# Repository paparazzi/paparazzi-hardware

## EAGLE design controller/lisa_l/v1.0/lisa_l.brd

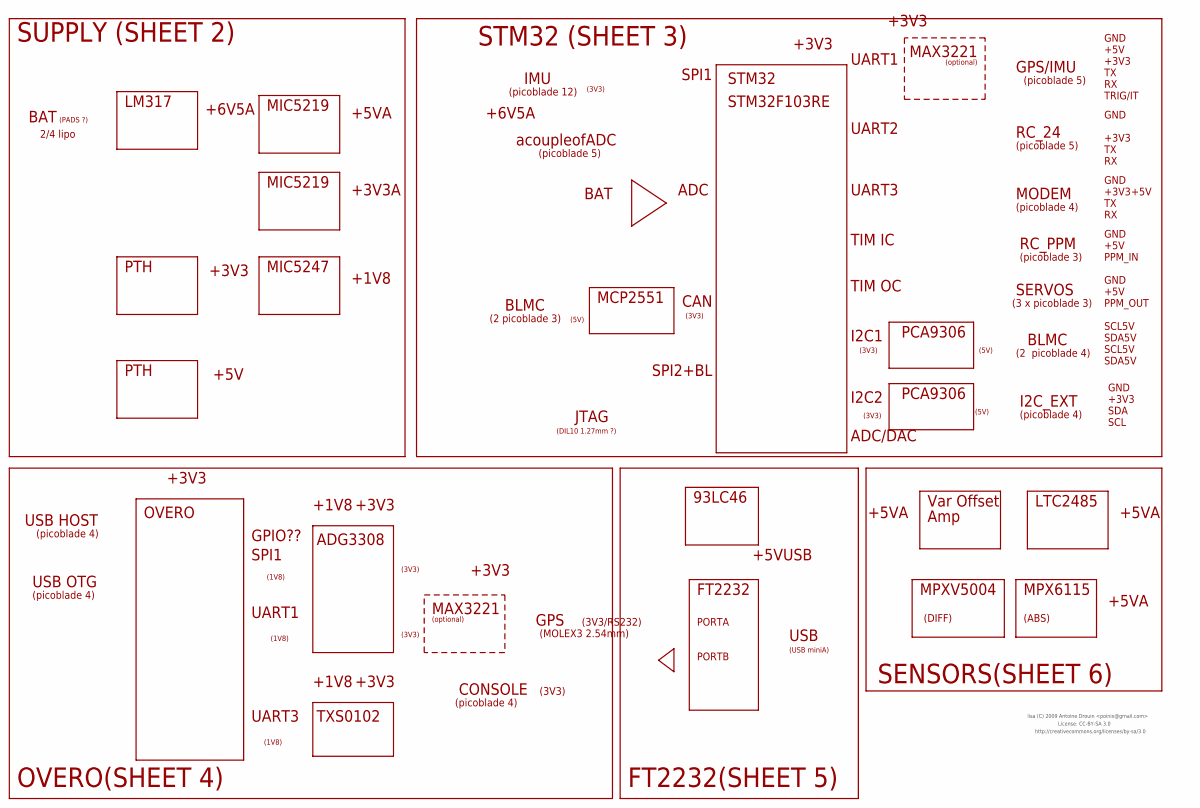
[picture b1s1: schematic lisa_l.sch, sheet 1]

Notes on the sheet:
SUPPLY (SHEET 2)
STM32 (SHEET 3)
OVERO(SHEET 4)
UART3
ADG3308
SPI1
UART1
OVERO
STM32
PTH
LM317
+5V
+3V3
+6V5A
BAT
IMU
MAX3221
GPS
(3V3/RS232)
(1V8)
(3V3)
SPI2+BL
SENSORS(SHEET 6)
JTAG
(PADS ?)
(picoblade 12)
2/4 lipo
(DIL10 1.27mm ?)
GPS/IMU
(picoblade 5)
(MOLEX3 2.54mm)
UART2
MODEM
TIM IC
RC_PPM
(picoblade 3)
FT2232
TIM OC
SERVOS
(3 x picoblade 3)

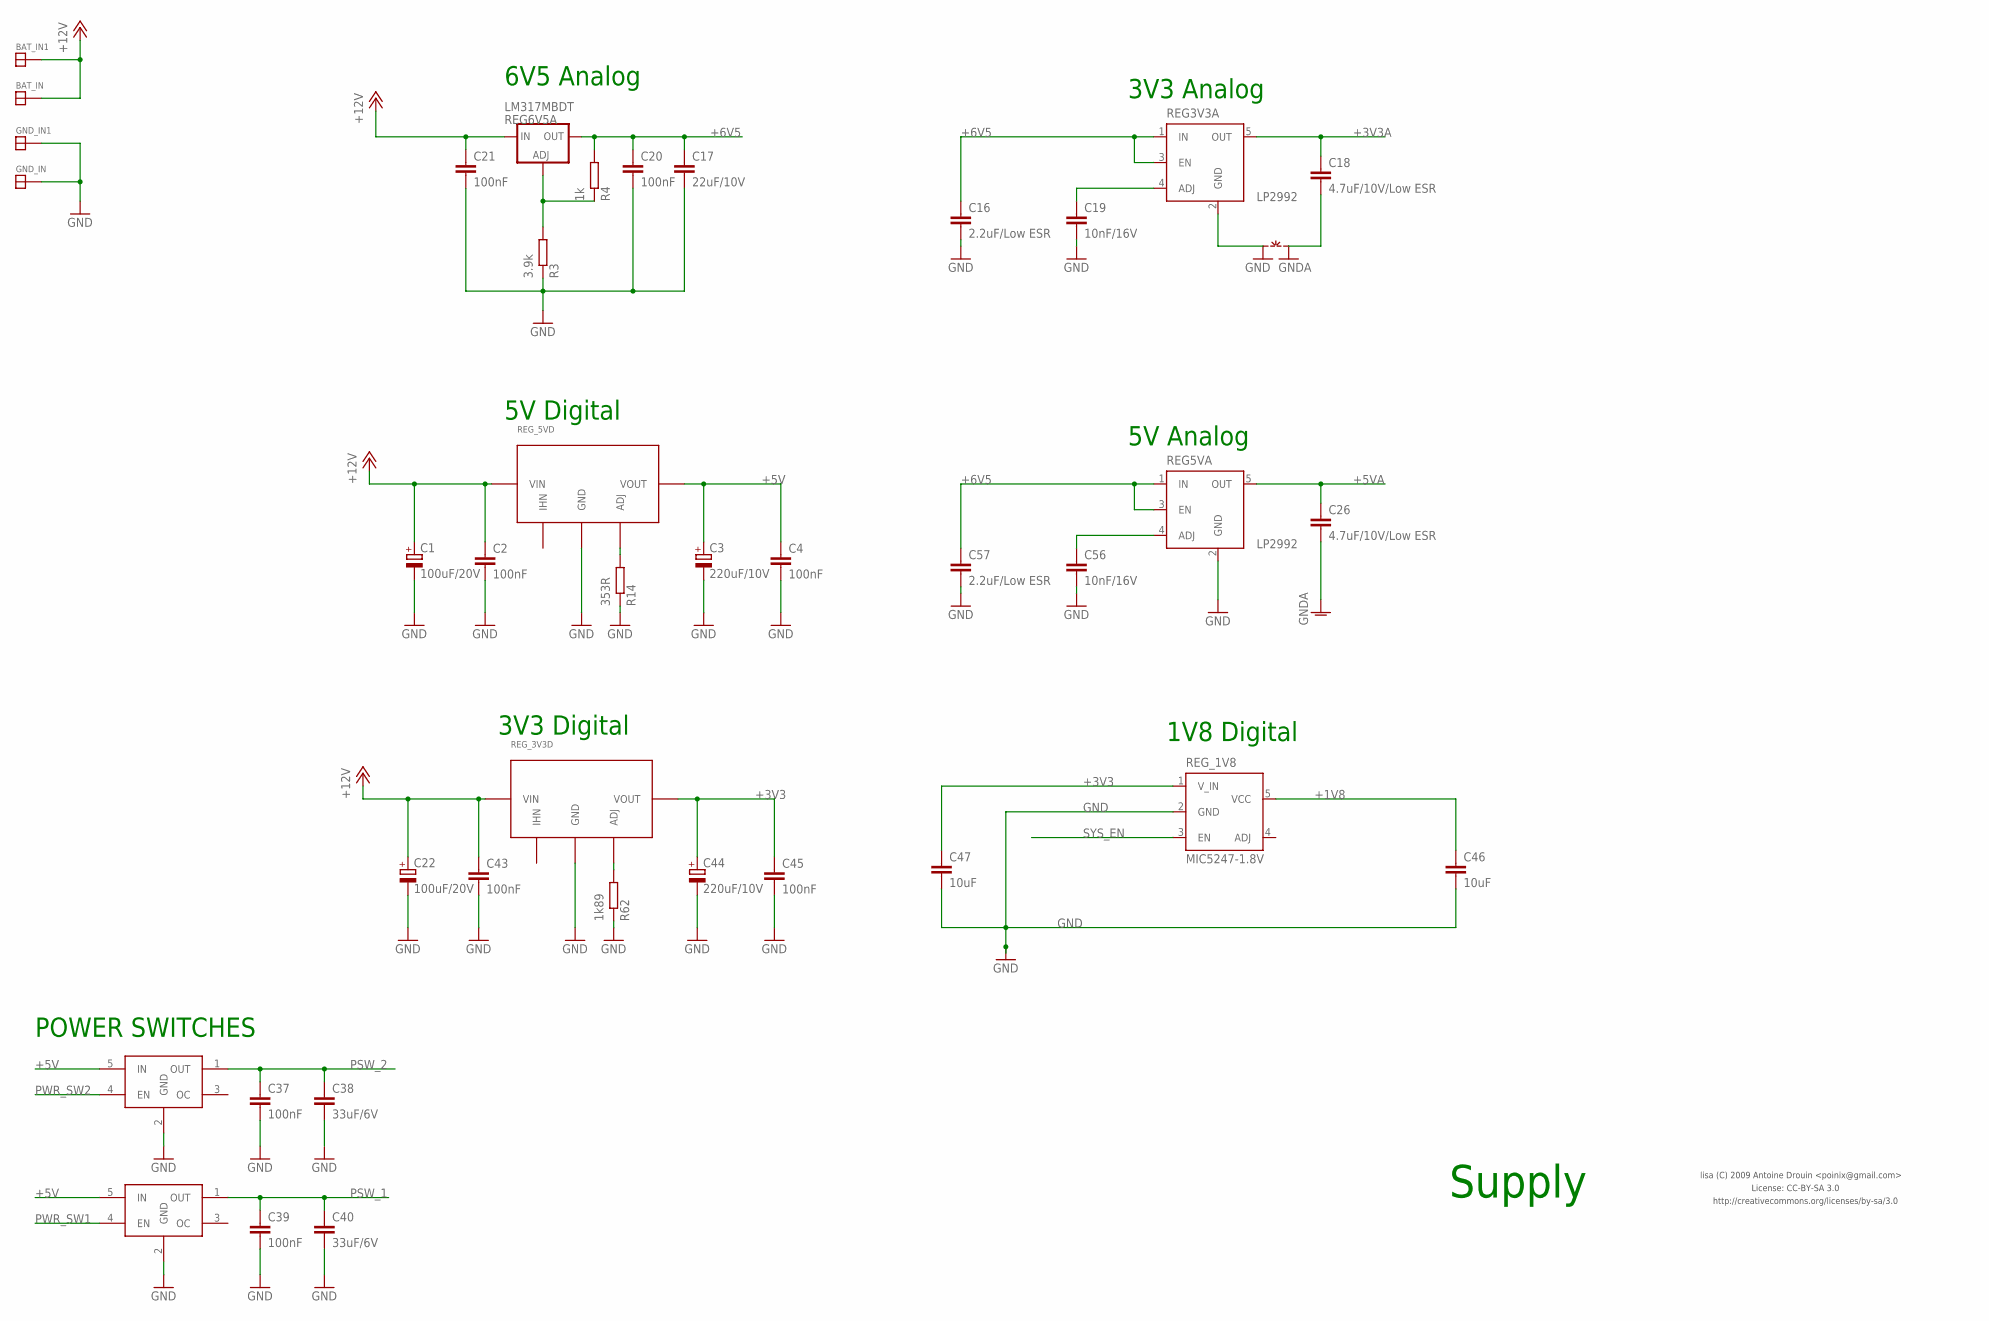
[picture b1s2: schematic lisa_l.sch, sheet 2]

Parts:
BAT_IN, BAT_IN1: SOLDER_PAD150_75; SOLD_PAD_150_75
C1, C22: 100uF/20V; 7343/D
C2, C4, C20, C21, C37, C39, C43, C45: 100nF; 0603-CAP
C3, C44: 220uF/10V; 7343/D
C16, C57: 2.2uF/Low ESR; 0603-CAP
C17: 22uF/10V; 1206-CAP
C18, C26: 4.7uF/10V/Low ESR; 0603-CAP
C19, C56: 10nF/16V; 0603-CAP
C38, C40: 33uF/6V; 1206-CAP
C46, C47: 10uF; 0603-CAP
GND_IN, GND_IN1: SOLDER_PAD150_75; SOLD_PAD_150_75
PWS1, PWS2: TPS2051B; SOT23-5L
R3: 3.9k; 0603-RES
R4: 1k; 0603-RES
R14: 353R; 0603-RES
R62: 1k89; 0603-RES
REG3V3A, REG5VA: LP2992; SOT23-5
REG6V5A: LM317MBDT; DPACK
REG_1V8: MIC5247-1.8V; SOT-23-5
REG_3V3D, REG_5VD: PTHTH; PTH_TH
~NUDEV~1: GND-GNDA

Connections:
+1V8: C46.P$1 (1), REG_1V8.5 (VCC); also elsewhere on the board
+3V3: C44.+, C45.P$1 (1), C47.P$1 (1), REG_1V8.1 (V_IN), REG_3V3D.P$3 (VOUT); also elsewhere on the board
+3V3A: C18.P$1 (1), REG3V3A.5 (OUT); also elsewhere on the board
+5V: C3.+, C4.P$1 (1), PWS1.5 (IN), PWS2.5 (IN), REG_5VD.P$3 (VOUT); also elsewhere on the board
+5VA: C26.P$1 (1), REG5VA.5 (OUT); also elsewhere on the board
+6V5: C16.P$1 (1), C17.P$1 (1), C20.P$1 (1), C57.P$1 (1), R4.P$2 (2), REG3V3A.1 (IN), REG3V3A.3 (EN), REG5VA.1 (IN), REG5VA.3 (EN), REG6V5A.4 (OUT); also elsewhere on the board
+12V: BAT_IN.P$1, BAT_IN1.P$1, C1.+, C2.P$1 (1), C21.P$1 (1), C22.+, C43.P$1 (1), REG6V5A.3 (IN), REG_3V3D.P$1 (VIN), REG_5VD.P$1 (VIN); also elsewhere on the board
GND: C1.-, C2.P$2 (2), C3.-, C4.P$2 (2), C16.P$2 (2), C17.P$2 (2), C19.P$2 (2), C20.P$2 (2), C21.P$2 (2), C22.-, C37.P$2 (2), C38.P$2 (2), C39.P$2 (2), C40.P$2 (2), C43.P$2 (2), C44.-, C45.P$2 (2), C46.P$2 (2), C47.P$2 (2), C56.P$2 (2), C57.P$2 (2), GND_IN.P$1, GND_IN1.P$1, PWS1.2 (GND), PWS2.2 (GND), R3.P$1 (1), R14.P$1 (1), R62.P$1 (1), REG3V3A.2 (GND), REG5VA.2 (GND), REG_1V8.2 (GND), REG_3V3D.P$2 (GND), REG_5VD.P$2 (GND), ~NUDEV~1.GND; also elsewhere on the board
GNDA: C18.P$2 (2), C26.P$2 (2), ~NUDEV~1.GNDA; also elsewhere on the board
unnamed: R62.P$2 (2), REG_3V3D.P$4 (ADJ)
unnamed: C56.P$1 (1), REG5VA.4 (ADJ)
unnamed: C19.P$1 (1), REG3V3A.4 (ADJ)
unnamed: R3.P$2 (2), R4.P$1 (1), REG6V5A.1 (ADJ)
PSW_1: C39.P$1 (1), C40.P$1 (1), PWS1.1 (OUT); also elsewhere on the board
PSW_2: C37.P$1 (1), C38.P$1 (1), PWS2.1 (OUT); also elsewhere on the board
PWR_SW1: PWS1.4 (EN); also elsewhere on the board
PWR_SW2: PWS2.4 (EN); also elsewhere on the board
RIPRIP: R14.P$2 (2), REG_5VD.P$4 (ADJ)
SYS_EN: REG_1V8.3 (EN); also elsewhere on the board

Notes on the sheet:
5V Digital
6V5 Analog
3V3 Analog
POWER SWITCHES
3V3 Digital
1V8 Digital
Supply
License: CC-BY-SA 3.0
http://creativecommons.org/licenses/by-sa/3.0
lisa (C) 2009 Antoine Drouin <poinix@gmail.com>
5V Analog

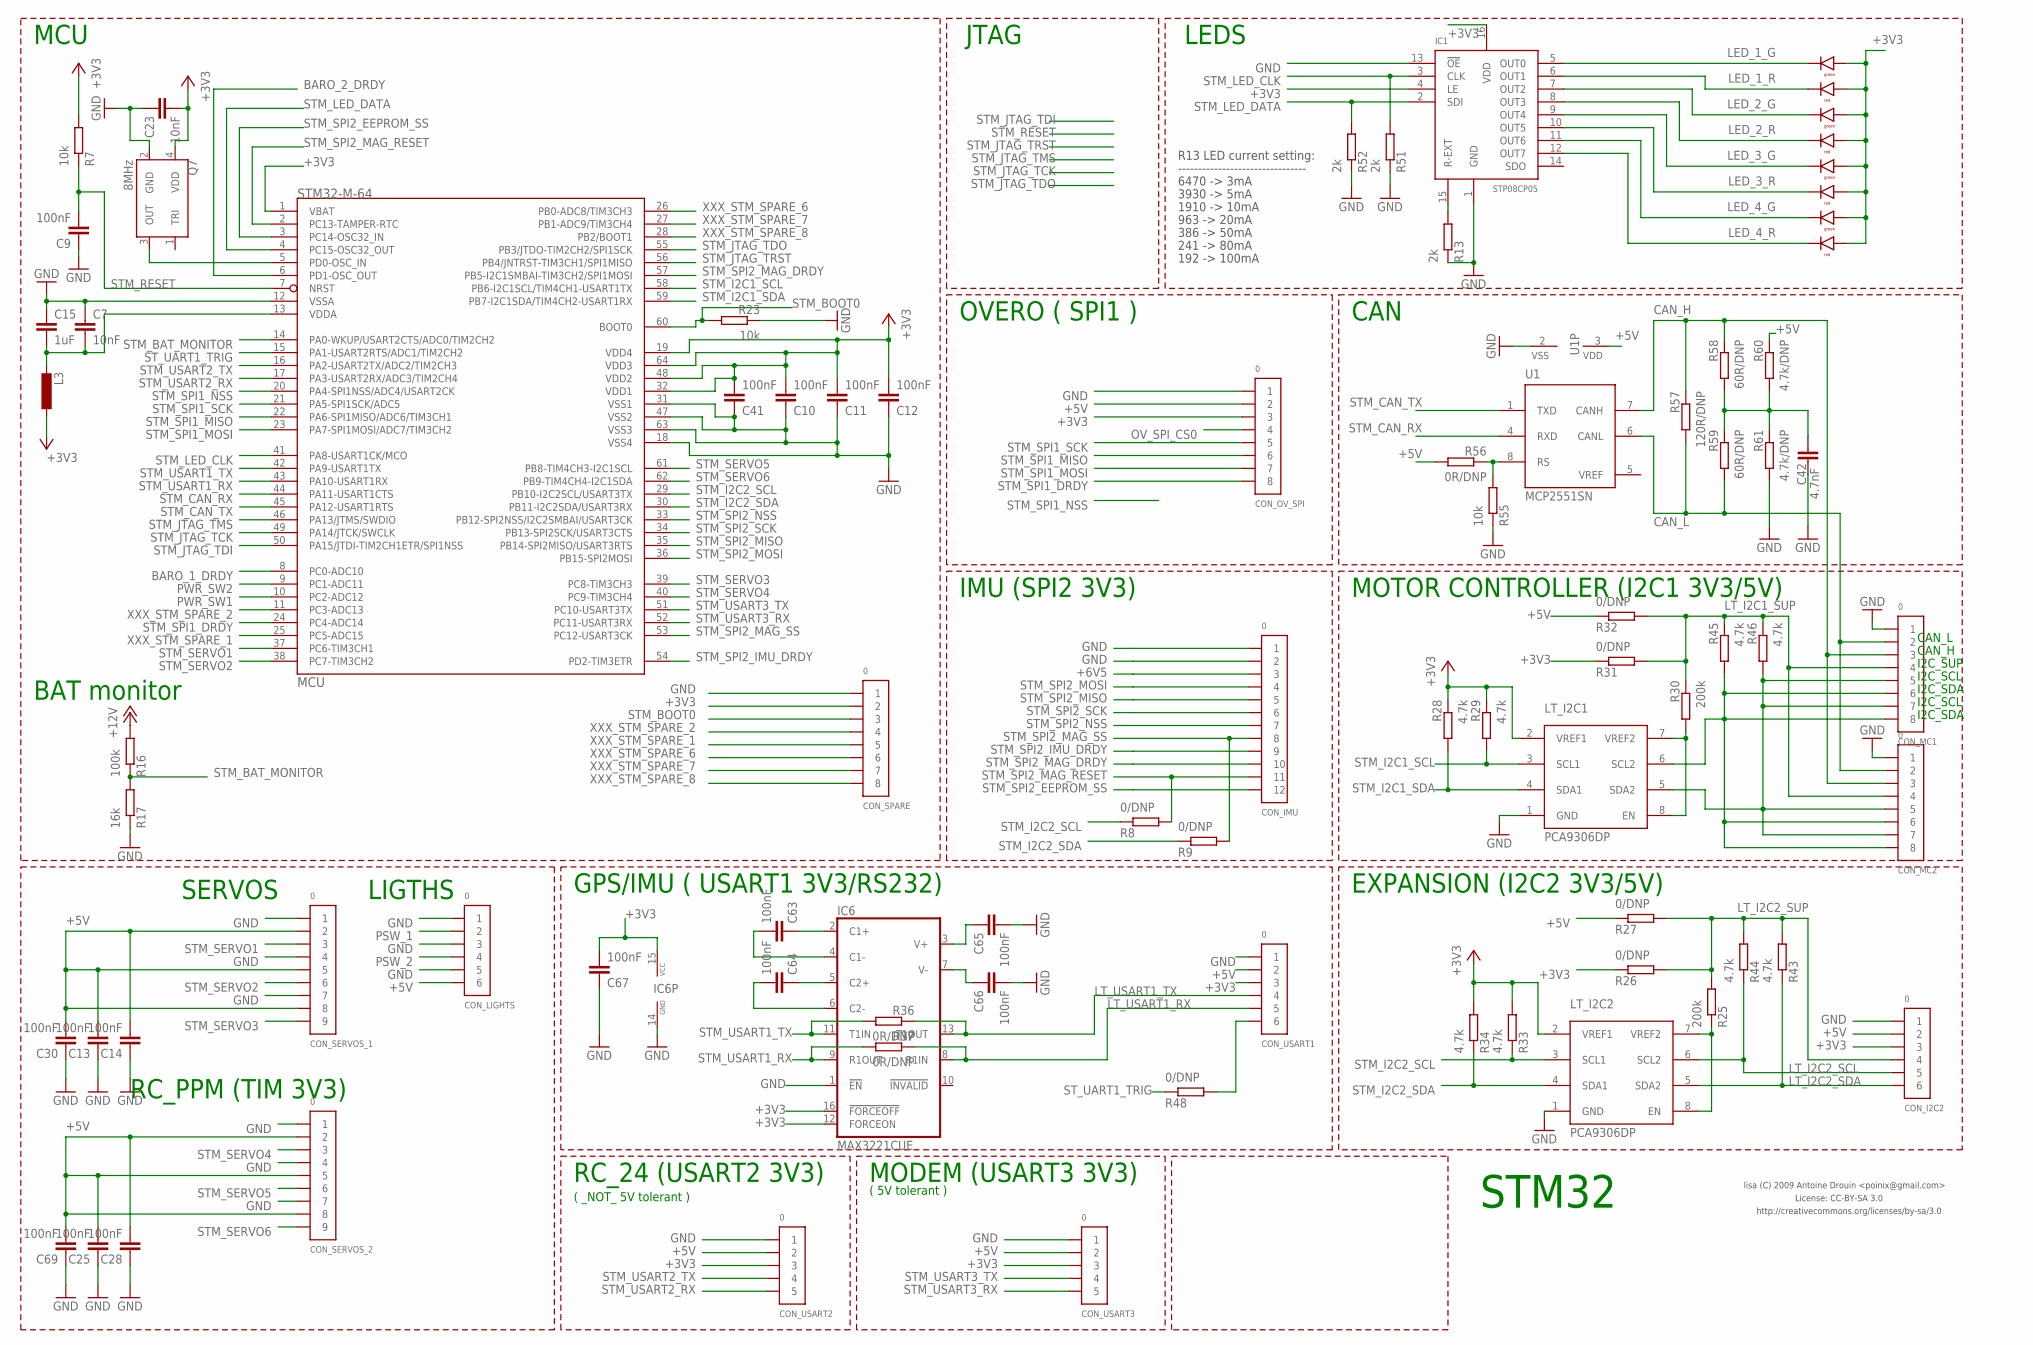
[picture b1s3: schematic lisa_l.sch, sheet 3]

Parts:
C7, C23: 10nF; 0603-CAP
C9, C10, C11, C12, C13, C14, C25, C28, C30, C41, C63, C64, C65, C66, C67, C69: 100nF; 0603-CAP
C15: 1uF; 0603-CAP
C42: 4.7nF; 0603-CAP
CON_I2C2: 0; PB-53261-06
CON_IMU: 0; PB-53398-12
CON_LIGHTS: 0; PB-53261-06
CON_MC1, CON_MC2: 0; PB-53261-08
CON_OV_SPI: 0; PB-53398-08
CON_SERVOS_1, CON_SERVOS_2: 0; PB-53261-09
CON_SPARE: 0; PB-53261-08
CON_USART1: 0; PB-53398-06
CON_USART2, CON_USART3: 0; PB-53261-05
IC1: STP08CP05; TSSOP16
IC6: MAX3221CUE; TSSOP16
L3: INDUCTOR-0603; 0603-IND
LED_1, LED_2, LED_3, LED_4: LED_DUO; DUO_LED
LT_I2C1, LT_I2C2: PCA9306DP; TSSOP_B3
MCU: STM32-M-64; LQFP64
Q7: 8MHz; ASE_OSCILLATOR
R7, R23, R55: 10k; 0603-RES
R8, R9, R26, R27, R31, R32, R48: 0/DNP; 0603-RES
R13, R51, R52: 2k; 0603-RES
R16: 100k; 0603-RES
R17: 16k; 0603-RES
R25, R30: 200k; 0603-RES
R28, R29, R33, R34, R43, R44, R45, R46: 4.7k; 0603-RES
R36, R37, R56: 0R/DNP; 0603-RES
R57: 120R/DNP; 0603-RES
R58, R59: 60R/DNP; 0603-RES
R60, R61: 4.7k/DNP; 0603-RES
U1: MCP2551SN; SO-08

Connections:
+3V3: C10.P$2 (2), C11.P$2 (2), C12.P$2 (2), C23.P$2 (2), C41.P$2 (2), C67.P$2 (2), CON_I2C2.3, CON_OV_SPI.3, CON_SPARE.2, CON_USART1.3, CON_USART2.3, CON_USART3.3, IC1.4 (LE), IC1.16 (VDD), IC6.12 (FORCEON), IC6.15 (VCC), IC6.16 (!FORCEOFF), L3.P$1 (1), LED_1.1, LED_1.4, LED_2.1, LED_2.4, LED_3.1, LED_3.4, LED_4.1, LED_4.4, LT_I2C1.2 (VREF1), LT_I2C2.2 (VREF1), MCU.1 (VBAT), MCU.19 (VDD4), MCU.32 (VDD1), MCU.48 (VDD2), MCU.64 (VDD3), Q7.4 (VDD), R7.P$2 (2), R26.P$1 (1), R28.P$1 (1), R29.P$1 (1), R31.P$1 (1), R33.P$2 (2), R34.P$2 (2); also elsewhere on the board
+5V: C13.P$2 (2), C14.P$2 (2), C25.P$2 (2), C28.P$2 (2), C30.P$2 (2), C69.P$2 (2), CON_I2C2.2, CON_LIGHTS.6, CON_OV_SPI.2, CON_SERVOS_1.2, CON_SERVOS_1.5, CON_SERVOS_1.8, CON_SERVOS_2.2, CON_SERVOS_2.5, CON_SERVOS_2.8, CON_USART1.2, CON_USART2.2, CON_USART3.2, R27.P$1 (1), R32.P$1 (1), R56.P$2 (2), R60.P$1 (1), U1.3 (VDD); also elsewhere on the board
+6V5: CON_IMU.3; also elsewhere on the board
+12V: R16.P$2 (2); also elsewhere on the board
BARO_1_DRDY: MCU.8 (PC0-ADC10); also elsewhere on the board
BARO_2_DRDY: MCU.6 (PD1-OSC_OUT); also elsewhere on the board
CAN_H: CON_MC1.3, CON_MC2.3, R57.P$1 (1), R58.P$1 (1), U1.7 (CANH)
CAN_L: CON_MC1.2, CON_MC2.2, R57.P$2 (2), R59.P$2 (2), U1.6 (CANL)
GND: C7.P$1 (1), C9.P$1 (1), C10.P$1 (1), C11.P$1 (1), C12.P$1 (1), C13.P$1 (1), C14.P$1 (1), C15.P$1 (1), C23.P$1 (1), C25.P$1 (1), C28.P$1 (1), C30.P$1 (1), C41.P$1 (1), C42.P$1 (1), C65.P$2 (2), C66.P$2 (2), C67.P$1 (1), C69.P$1 (1), CON_I2C2.1, CON_IMU.1, CON_IMU.2, CON_LIGHTS.1, CON_LIGHTS.3, CON_LIGHTS.5, CON_MC1.1, CON_MC2.1, CON_OV_SPI.1, CON_SERVOS_1.1, CON_SERVOS_1.4, CON_SERVOS_1.7, CON_SERVOS_2.1, CON_SERVOS_2.4, CON_SERVOS_2.7, CON_SPARE.1, CON_USART1.1, CON_USART2.1, CON_USART3.1, IC1.1 (GND), IC1.13 (!OE), IC6.1 (!EN), IC6.14 (GND), LT_I2C1.1 (GND), LT_I2C2.1 (GND), MCU.12 (VSSA), MCU.18 (VSS4), MCU.31 (VSS1), MCU.47 (VSS2), MCU.63 (VSS3), Q7.2 (GND), R13.P$1 (1), R17.P$1 (1), R23.P$1 (1), R51.P$1 (1), R52.P$1 (1), R55.P$1 (1), R61.P$2 (2), U1.2 (VSS); also elsewhere on the board
INT/TRIGGER: CON_USART1.6, R48.P$2 (2)
LED_1_G: IC1.5 (OUT0), LED_1.3
LED_1_R: IC1.6 (OUT1), LED_1.2
LED_2_G: IC1.7 (OUT2), LED_2.3
LED_2_R: IC1.8 (OUT3), LED_2.2
LED_3_G: IC1.9 (OUT4), LED_3.3
LED_3_R: IC1.10 (OUT5), LED_3.2
LED_4_G: IC1.11 (OUT6), LED_4.3
LED_4_R: IC1.12 (OUT7), LED_4.2
LT_I2C1_SUP: CON_MC1.4, CON_MC2.4, R30.P$1 (1), R31.P$2 (2), R32.P$2 (2), R45.P$1 (1), R46.P$1 (1)
LT_I2C2_SCL: CON_I2C2.5, LT_I2C2.6 (SCL2), R44.P$1 (1)
LT_I2C2_SDA: CON_I2C2.6, LT_I2C2.5 (SDA2), R43.P$1 (1)
LT_I2C2_SUP: CON_I2C2.4, R25.P$2 (2), R26.P$2 (2), R27.P$2 (2), R43.P$2 (2), R44.P$2 (2)
LT_USART1_RX: CON_USART1.5, IC6.8 (R1IN), R37.P$1 (1)
LT_USART1_TX: CON_USART1.4, IC6.13 (T1OUT), R36.P$1 (1)
unnamed: IC1.15 (R-EXT), R13.P$2 (2)
unnamed: MCU.5 (PD0-OSC_IN), Q7.3 (OUT)
unnamed: LT_I2C1.7 (VREF2), LT_I2C1.8 (EN), R30.P$2 (2)
unnamed: R55.P$2 (2), R56.P$1 (1), U1.8 (RS)
unnamed: LT_I2C2.7 (VREF2), LT_I2C2.8 (EN), R25.P$1 (1)
unnamed: C42.P$2 (2), R58.P$2 (2), R59.P$1 (1), R60.P$2 (2), R61.P$1 (1)
unnamed: C63.P$1 (1), IC6.2 (C1+)
unnamed: C63.P$2 (2), IC6.4 (C1-)
unnamed: C64.P$1 (1), IC6.5 (C2+)
unnamed: C64.P$2 (2), IC6.6 (C2-)
unnamed: C66.P$1 (1), IC6.7 (V-)
unnamed: C65.P$1 (1), IC6.3 (V+)
OV_SPI_CS0: CON_OV_SPI.4; also elsewhere on the board
PSW_1: CON_LIGHTS.2; also elsewhere on the board
PSW_2: CON_LIGHTS.4; also elsewhere on the board
PWR_SW1: MCU.10 (PC2-ADC12); also elsewhere on the board
PWR_SW2: MCU.9 (PC1-ADC11); also elsewhere on the board
SCL_0_TRANSLATED: CON_MC1.6, CON_MC1.8, CON_MC2.6, CON_MC2.8, LT_I2C1.6 (SCL2), R45.P$2 (2)
SDA_0_TRANSLATED: CON_MC1.5, CON_MC1.7, CON_MC2.5, CON_MC2.7, LT_I2C1.5 (SDA2), R46.P$2 (2)
STM_BAT_MONITOR: MCU.14 (PA0-WKUP/USART2CTS/ADC0/TIM2CH2), R16.P$1 (1), R17.P$2 (2)
STM_BOOT0: CON_SPARE.3, MCU.60 (BOOT0), R23.P$2 (2)
STM_CAN_RX: MCU.44 (PA11-USART1CTS), U1.4 (RXD)
STM_CAN_TX: MCU.45 (PA12-USART1RTS), U1.1 (TXD)
STM_I2C1_SCL: LT_I2C1.3 (SCL1), MCU.58 (PB6-I2C1SCL/TIM4CH1-USART1TX), R29.P$2 (2)
STM_I2C1_SDA: LT_I2C1.4 (SDA1), MCU.59 (PB7-I2C1SDA/TIM4CH2-USART1RX), R28.P$2 (2)
STM_I2C2_SCL: LT_I2C2.3 (SCL1), MCU.29 (PB10-I2C2SCL/USART3TX), R8.P$1 (1), R33.P$1 (1); also elsewhere on the board
STM_I2C2_SDA: LT_I2C2.4 (SDA1), MCU.30 (PB11-I2C2SDA/USART3RX), R9.P$1 (1), R34.P$1 (1); also elsewhere on the board
STM_JTAG_TCK: MCU.49 (PA14/JTCK/SWCLK); also elsewhere on the board
STM_JTAG_TDI: MCU.50 (PA15/JTDI-TIM2CH1ETR/SPI1NSS); also elsewhere on the board
STM_JTAG_TDO: MCU.55 (PB3/JTDO-TIM2CH2/SPI1SCK); also elsewhere on the board
STM_JTAG_TMS: MCU.46 (PA13/JTMS/SWDIO); also elsewhere on the board
STM_JTAG_TRST: MCU.56 (PB4/JNTRST-TIM3CH1/SPI1MISO); also elsewhere on the board
STM_LED_CLK: IC1.3 (CLK), MCU.41 (PA8-USART1CK/MCO), R51.P$2 (2)
STM_LED_DATA: IC1.2 (SDI), MCU.4 (PC15-OSC32_OUT), R52.P$2 (2)
STM_RESET: C9.P$2 (2), MCU.7 (NRST), R7.P$1 (1); also elsewhere on the board
STM_SERVO1: CON_SERVOS_1.3, MCU.37 (PC6-TIM3CH1)
STM_SERVO2: CON_SERVOS_1.6, MCU.38 (PC7-TIM3CH2)
STM_SERVO3: CON_SERVOS_1.9, MCU.39 (PC8-TIM3CH3)
STM_SERVO4: CON_SERVOS_2.3, MCU.40 (PC9-TIM3CH4)
STM_SERVO5: CON_SERVOS_2.6, MCU.61 (PB8-TIM4CH3-I2C1SCL)
STM_SERVO6: CON_SERVOS_2.9, MCU.62 (PB9-TIM4CH4-I2C1SDA)
STM_SPI1_DRDY: CON_OV_SPI.8, MCU.24 (PC4-ADC14); also elsewhere on the board
STM_SPI1_MISO: CON_OV_SPI.6, MCU.22 (PA6-SPI1MISO/ADC6/TIM3CH1); also elsewhere on the board
STM_SPI1_MOSI: CON_OV_SPI.7, MCU.23 (PA7-SPI1MOSI/ADC7/TIM3CH2); also elsewhere on the board
STM_SPI1_NSS: MCU.20 (PA4-SPI1NSS/ADC4/USART2CK); also elsewhere on the board
STM_SPI1_SCK: CON_OV_SPI.5, MCU.21 (PA5-SPI1SCK/ADC5); also elsewhere on the board
STM_SPI2_EEPROM_SS: CON_IMU.12, MCU.3 (PC14-OSC32_IN)
STM_SPI2_IMU_DRDY: CON_IMU.9, MCU.54 (PD2-TIM3ETR)
STM_SPI2_MAG_DRDY: CON_IMU.10, MCU.57 (PB5-I2C1SMBAI-TIM3CH2/SPI1MOSI)
STM_SPI2_MAG_RESET: CON_IMU.11, MCU.2 (PC13-TAMPER-RTC), R8.P$2 (2)
STM_SPI2_MAG_SS: CON_IMU.8, MCU.53 (PC12-USART3CK), R9.P$2 (2)
STM_SPI2_MISO: CON_IMU.5, MCU.35 (PB14-SPI2MISO/USART3RTS)
STM_SPI2_MOSI: CON_IMU.4, MCU.36 (PB15-SPI2MOSI)
STM_SPI2_NSS: CON_IMU.7, MCU.33 (PB12-SPI2NSS/I2C2SMBAI/USART3CK)
STM_SPI2_SCK: CON_IMU.6, MCU.34 (PB13-SPI2SCK/USART3CTS)
STM_USART1_RX: IC6.9 (R1OUT), MCU.43 (PA10-USART1RX), R37.P$2 (2)
STM_USART1_TX: IC6.11 (T1IN), MCU.42 (PA9-USART1TX), R36.P$2 (2)
STM_USART2_RX: CON_USART2.5, MCU.17 (PA3-USART2RX/ADC3/TIM2CH4)
STM_USART2_TX: CON_USART2.4, MCU.16 (PA2-USART2TX/ADC2/TIM2CH3)
STM_USART3_RX: CON_USART3.5, MCU.52 (PC11-USART3RX)
STM_USART3_TX: CON_USART3.4, MCU.51 (PC10-USART3TX)
ST_UART1_TRIG: MCU.15 (PA1-USART2RTS/ADC1/TIM2CH2), R48.P$1 (1)
VDDA: C7.P$2 (2), C15.P$2 (2), L3.P$2 (2), MCU.13 (VDDA)
VREF: U1.5 (VREF)
XXX_STM_SPARE_1: CON_SPARE.5, MCU.25 (PC5-ADC15)
XXX_STM_SPARE_2: CON_SPARE.4, MCU.11 (PC3-ADC13)
XXX_STM_SPARE_6: CON_SPARE.6, MCU.26 (PB0-ADC8/TIM3CH3)
XXX_STM_SPARE_7: CON_SPARE.7, MCU.27 (PB1-ADC9/TIM3CH4)
XXX_STM_SPARE_8: CON_SPARE.8, MCU.28 (PB2/BOOT1)

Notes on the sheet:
MCU
LEDS
OVERO ( SPI1 )
EXPANSION (I2C2 3V3/5V)
MOTOR CONTROLLER (I2C1 3V3/5V)
GPS/IMU ( USART1 3V3/RS232)
IMU (SPI2 3V3)
RC_24 (USART2 3V3)
SERVOS
CAN
BAT monitor
STM32
JTAG
MODEM (USART3 3V3)
RC_PPM (TIM 3V3)
License: CC-BY-SA 3.0
http://creativecommons.org/licenses/by-sa/3.0
lisa (C) 2009 Antoine Drouin <poinix@gmail.com>
CAN_L
CAN_H
I2C_SUP
I2C_SCL
I2C_SDA
LIGTHS
R13 LED current setting:
--------------------------------
6470 -> 3mA
3930 -> 5mA
1910 -> 10mA
963 -> 20mA
386 -> 50mA
241 -> 80mA
192 -> 100mA
( 5V tolerant )
( _NOT_ 5V tolerant )

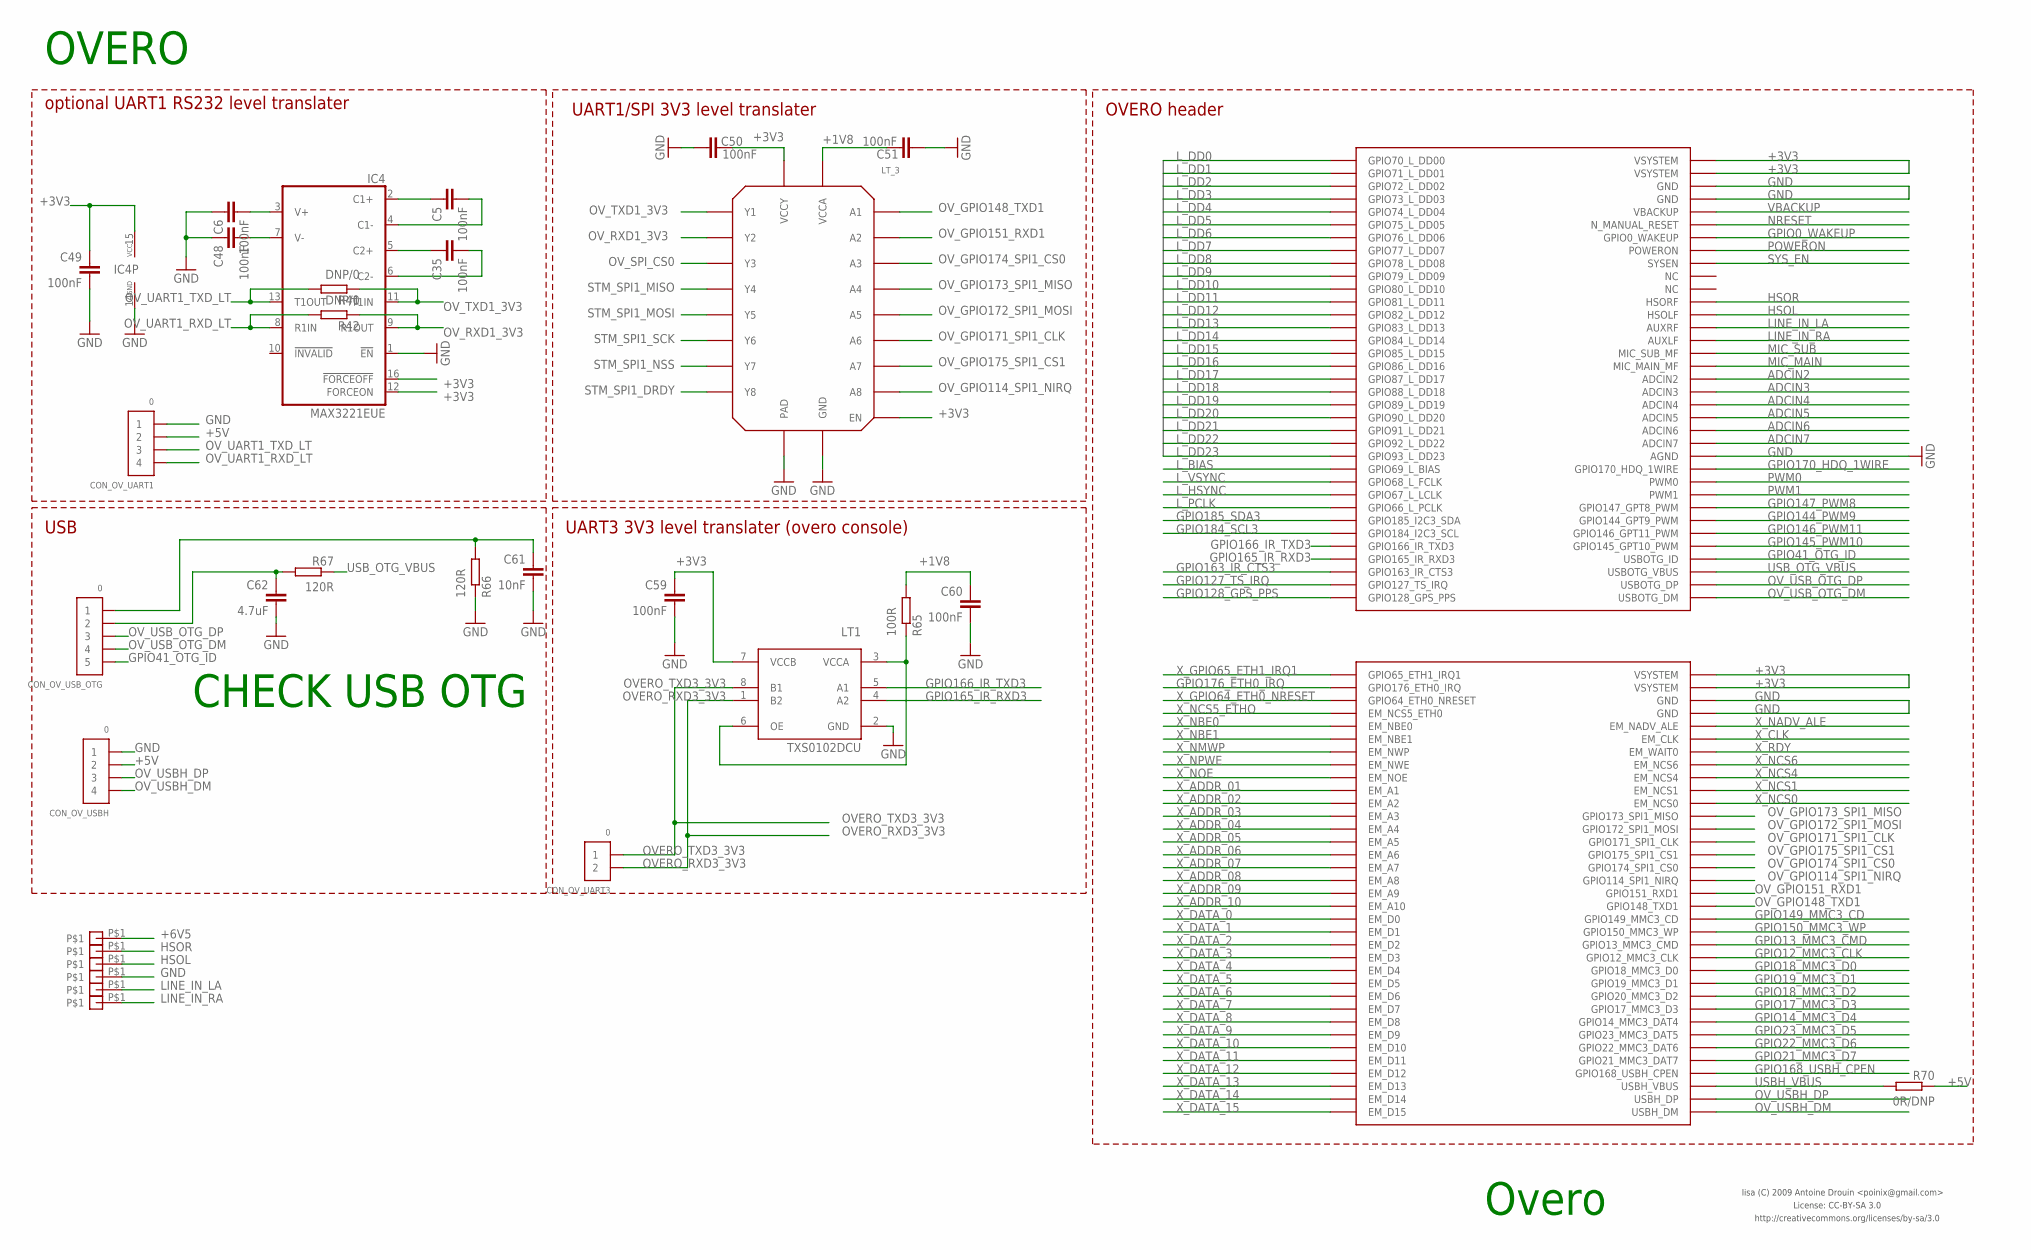
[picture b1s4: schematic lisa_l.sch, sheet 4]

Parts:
C5, C6, C35, C48, C49, C50, C51, C59, C60: 100nF; 0603-CAP
C61: 10nF; 0603-CAP
C62: 4.7uF; 0603-CAP
CON_OV_UART1: 0; PB-53261-04
CON_OV_UART3: 0; PB-53261-02
CON_OV_USBH: 0; PB-53261-04
CON_OV_USB_OTG: 0; PB-53261-05
IC4: MAX3221EUE; TSSOP16
J3&4: OVERO
LT1: TXS0102DCU; US8
LT_3: AD3308BCPZ; LFCSP-20
R41, R42: DNP/0; 0603-RES
R65: 100R; 0603-RES
R66, R67: 120R; 0603-RES
R70: 0R/DNP; 0603-RES
U$1, U$2, U$3, U$4, U$5, U$6: SOLDER_PAD; SOLDER_PAD_SMALL

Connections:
+1V8: C51.P$1 (1), C60.P$1 (1), LT_3.P$19 (VCCA), R65.P$2 (2); also elsewhere on the board
+3V3: C49.P$1 (1), C50.P$1 (1), C59.P$1 (1), IC4.12 (FORCEON), IC4.15 (VCC), IC4.16 (!FORCEOFF), J3&4.VSYSTEM@1 (VSYSTEM), J3&4.VSYSTEM@2 (VSYSTEM), J3&4.VSYSTEM@66 (VSYSTEM), J3&4.VSYSTEM@67 (VSYSTEM), LT1.7 (VCCB), LT_3.P$8 (EN), LT_3.P$18 (VCCY); also elsewhere on the board
+5V: CON_OV_UART1.2, CON_OV_USBH.2, R70.P$1 (1); also elsewhere on the board
+6V5: U$1.P$1; also elsewhere on the board
ADCIN2: J3&4.ADCIN2
ADCIN3: J3&4.ADCIN3
ADCIN4: J3&4.ADCIN4
ADCIN5: J3&4.ADCIN5
ADCIN6: J3&4.ADCIN6
ADCIN7: J3&4.ADCIN7
GND: C6.P$1 (1), C48.P$1 (1), C49.P$2 (2), C50.P$2 (2), C51.P$2 (2), C59.P$2 (2), C60.P$2 (2), C61.P$2 (2), C62.P$2 (2), CON_OV_UART1.1, CON_OV_USBH.1, IC4.1 (!EN), IC4.14 (GND), J3&4.AGND, J3&4.GND, J3&4.GND@33 (GND), J3&4.GND@56 (GND), J3&4.GND@70 (GND), LT1.2 (GND), LT_3.P$9 (GND), LT_3.P$21 (PAD), R66.P$1 (1), U$4.P$1; also elsewhere on the board
GPIO0_WAKEUP: J3&4.GPIO0_WAKEUP
GPIO12_MMC3_CLK: J3&4.GPIO12_MMC3_CLK
GPIO13_MMC3_CMD: J3&4.GPIO13_MMC3_CMD
GPIO14_MMC3_D4: J3&4.GPIO14_MMC3_DAT4
GPIO17_MMC3_D3: J3&4.GPIO17_MMC3_D3
GPIO18_MMC3_D0: J3&4.GPIO18_MMC3_D0
GPIO18_MMC3_D2: J3&4.GPIO20_MMC3_D2
GPIO19_MMC3_D1: J3&4.GPIO19_MMC3_D1
GPIO21_MMC3_D7: J3&4.GPIO21_MMC3_DAT7
GPIO22_MMC3_D6: J3&4.GPIO22_MMC3_DAT6
GPIO23_MMC3_D5: J3&4.GPIO23_MMC3_DAT5
GPIO41_OTG_ID: CON_OV_USB_OTG.5, J3&4.USBOTG_ID
GPIO127_TS_IRQ: J3&4.GPIO127_TS_IRQ
GPIO128_GPS_PPS: J3&4.GPIO128_GPS_PPS
GPIO144_PWM9: J3&4.GPIO144_GPT9_PWM
GPIO145_PWM10: J3&4.GPIO145_GPT10_PWM
GPIO146_PWM11: J3&4.GPIO146_GPT11_PWM
GPIO147_PWM8: J3&4.GPIO147_GPT8_PWM
GPIO149_MMC3_CD: J3&4.GPIO149_MMC3_CD
GPIO150_MMC3_WP: J3&4.GPIO150_MMC3_WP
GPIO163_IR_CTS3: J3&4.GPIO163_IR_CTS3
GPIO165_IR_RXD3: J3&4.GPIO165_IR_RXD3, LT1.4 (A2)
GPIO166_IR_TXD3: J3&4.GPIO166_IR_TXD3, LT1.5 (A1)
GPIO168_USBH_CPEN: J3&4.GPIO168_USBH_CPEN
GPIO170_HDQ_1WIRE: J3&4.GPIO170_HDQ_1WIRE
GPIO176_ETH0_IRQ: J3&4.GPIO176_ETH0_IRQ
GPIO184_SCL3: J3&4.GPIO184_I2C3_SCL
GPIO185_SDA3: J3&4.GPIO185_I2C3_SDA
HSOL: J3&4.HSOLF, U$3.P$1
HSOR: J3&4.HSORF, U$2.P$1
LINE_IN_LA: J3&4.AUXRF, U$5.P$1
LINE_IN_RA: J3&4.AUXLF, U$6.P$1
L_BIAS: J3&4.GPIO69_L_BIAS
L_DD0: J3&4.GPIO70_L_DD00
L_DD1: J3&4.GPIO71_L_DD01
L_DD2: J3&4.GPIO72_L_DD02
L_DD3: J3&4.GPIO73_L_DD03
L_DD4: J3&4.GPIO74_L_DD04
L_DD5: J3&4.GPIO75_L_DD05
L_DD6: J3&4.GPIO76_L_DD06
L_DD7: J3&4.GPIO77_L_DD07
L_DD8: J3&4.GPIO78_L_DD08
L_DD9: J3&4.GPIO79_L_DD09
L_DD10: J3&4.GPIO80_L_DD10
L_DD11: J3&4.GPIO81_L_DD11
L_DD12: J3&4.GPIO82_L_DD12
L_DD13: J3&4.GPIO83_L_DD13
L_DD14: J3&4.GPIO84_L_DD14
L_DD15: J3&4.GPIO85_L_DD15
L_DD16: J3&4.GPIO86_L_DD16
L_DD17: J3&4.GPIO87_L_DD17
L_DD18: J3&4.GPIO88_L_DD18
L_DD19: J3&4.GPIO89_L_DD19
L_DD20: J3&4.GPIO90_L_DD20
L_DD21: J3&4.GPIO91_L_DD21
L_DD22: J3&4.GPIO92_L_DD22
L_DD23: J3&4.GPIO93_L_DD23
L_HSYNC: J3&4.GPIO67_L_LCLK
L_PCLK: J3&4.GPIO66_L_PCLK
L_VSYNC: J3&4.GPIO68_L_FCLK
MIC_MAIN: J3&4.MIC_MAIN_MF
MIC_SUB: J3&4.MIC_SUB_MF
unnamed: C5.P$1 (1), IC4.2 (C1+)
unnamed: C5.P$2 (2), IC4.4 (C1-)
unnamed: C35.P$1 (1), IC4.5 (C2+)
unnamed: C35.P$2 (2), IC4.6 (C2-)
unnamed: C6.P$2 (2), IC4.3 (V+)
unnamed: C48.P$2 (2), IC4.7 (V-)
unnamed: C61.P$1 (1), CON_OV_USB_OTG.1, R66.P$2 (2)
unnamed: C62.P$1 (1), CON_OV_USB_OTG.2, R67.P$2 (2)
unnamed: LT1.3 (VCCA), LT1.6 (OE), R65.P$1 (1)
NRESET: J3&4.N_MANUAL_RESET
OVERO_RXD3_3V3: CON_OV_UART3.2, LT1.1 (B2); also elsewhere on the board
OVERO_TXD3_3V3: CON_OV_UART3.1, LT1.8 (B1); also elsewhere on the board
OV_GPIO114_SPI1_NIRQ: J3&4.GPIO114_SPI1_NIRQ, LT_3.P$7 (A8)
OV_GPIO148_TXD1: J3&4.GPIO148_TXD1, LT_3.P$20 (A1)
OV_GPIO151_RXD1: J3&4.GPIO151_RXD1, LT_3.P$1 (A2)
OV_GPIO171_SPI1_CLK: J3&4.GPIO171_SPI1_CLK, LT_3.P$5 (A6)
OV_GPIO172_SPI1_MOSI: J3&4.GPIO172_SPI1_MOSI, LT_3.P$4 (A5)
OV_GPIO173_SPI1_MISO: J3&4.GPIO173_SPI1_MISO, LT_3.P$3 (A4)
OV_GPIO174_SPI1_CS0: J3&4.GPIO174_SPI1_CS0, LT_3.P$2 (A3)
OV_GPIO175_SPI1_CS1: J3&4.GPIO175_SPI1_CS1, LT_3.P$6 (A7)
OV_RXD1_3V3: IC4.9 (R1OUT), LT_3.P$16 (Y2), R42.P$1 (1)
OV_SPI_CS0: LT_3.P$15 (Y3); also elsewhere on the board
OV_TXD1_3V3: IC4.11 (T1IN), LT_3.P$17 (Y1), R41.P$1 (1)
OV_UART1_RXD_LT: CON_OV_UART1.4, IC4.8 (R1IN), R42.P$2 (2)
OV_UART1_TXD_LT: CON_OV_UART1.3, IC4.13 (T1OUT), R41.P$2 (2)
OV_USBH_DM: CON_OV_USBH.4, J3&4.USBH_DM
OV_USBH_DP: CON_OV_USBH.3, J3&4.USBH_DP
OV_USB_OTG_DM: CON_OV_USB_OTG.4, J3&4.USBOTG_DM
OV_USB_OTG_DP: CON_OV_USB_OTG.3, J3&4.USBOTG_DP
POWERON: J3&4.POWERON
PWM0: J3&4.PWM0
PWM1: J3&4.PWM1
STM_SPI1_DRDY: LT_3.P$10 (Y8); also elsewhere on the board
STM_SPI1_MISO: LT_3.P$14 (Y4); also elsewhere on the board
STM_SPI1_MOSI: LT_3.P$13 (Y5); also elsewhere on the board
STM_SPI1_NSS: LT_3.P$11 (Y7); also elsewhere on the board
STM_SPI1_SCK: LT_3.P$12 (Y6); also elsewhere on the board
SYS_EN: J3&4.SYSEN; also elsewhere on the board
USBH_VBUS: J3&4.USBH_VBUS, R70.P$2 (2)
USB_OTG_VBUS: J3&4.USBOTG_VBUS, R67.P$1 (1)
VBACKUP: J3&4.VBACKUP
X_ADDR_01: J3&4.EM_A1
X_ADDR_02: J3&4.EM_A2
X_ADDR_03: J3&4.EM_A3
X_ADDR_04: J3&4.EM_A4
X_ADDR_05: J3&4.EM_A5
X_ADDR_06: J3&4.EM_A6
X_ADDR_07: J3&4.EM_A7
X_ADDR_08: J3&4.EM_A8
X_ADDR_09: J3&4.EM_A9
X_ADDR_10: J3&4.EM_A10
X_CLK: J3&4.EM_CLK
X_DATA_0: J3&4.EM_D0
X_DATA_1: J3&4.EM_D1
X_DATA_2: J3&4.EM_D2
X_DATA_3: J3&4.EM_D3
X_DATA_4: J3&4.EM_D4
X_DATA_5: J3&4.EM_D5
X_DATA_6: J3&4.EM_D6
X_DATA_7: J3&4.EM_D7
X_DATA_8: J3&4.EM_D8
X_DATA_9: J3&4.EM_D9
X_DATA_10: J3&4.EM_D10
X_DATA_11: J3&4.EM_D11
X_DATA_12: J3&4.EM_D12
X_DATA_13: J3&4.EM_D13
X_DATA_14: J3&4.EM_D14
X_DATA_15: J3&4.EM_D15
X_GPIO64_ETH0_NRESET: J3&4.GPIO64_ETH0_NRESET
X_GPIO65_ETH1_IRQ1: J3&4.GPIO65_ETH1_IRQ1
X_NADV_ALE: J3&4.EM_NADV_ALE
X_NBE0: J3&4.EM_NBE0
X_NBE1: J3&4.EM_NBE1
X_NCS0: J3&4.EM_NCS0
X_NCS1: J3&4.EM_NCS1
X_NCS4: J3&4.EM_NCS4
X_NCS5_ETHO: J3&4.EM_NCS5_ETH0
X_NCS6: J3&4.EM_NCS6
X_NMWP: J3&4.EM_NWP
X_NOE: J3&4.EM_NOE
X_NPWE: J3&4.EM_NWE
X_RDY: J3&4.EM_WAIT0

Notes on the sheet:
OVERO
optional UART1 RS232 level translater
Overo
UART1/SPI 3V3 level translater
UART3 3V3 level translater (overo console)
USB
OVERO header
License: CC-BY-SA 3.0
http://creativecommons.org/licenses/by-sa/3.0
lisa (C) 2009 Antoine Drouin <poinix@gmail.com>
CHECK USB OTG

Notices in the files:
controller/lisa_m/v2.0/lisa_m.sch:
(C) 2011 Transition Robotics
